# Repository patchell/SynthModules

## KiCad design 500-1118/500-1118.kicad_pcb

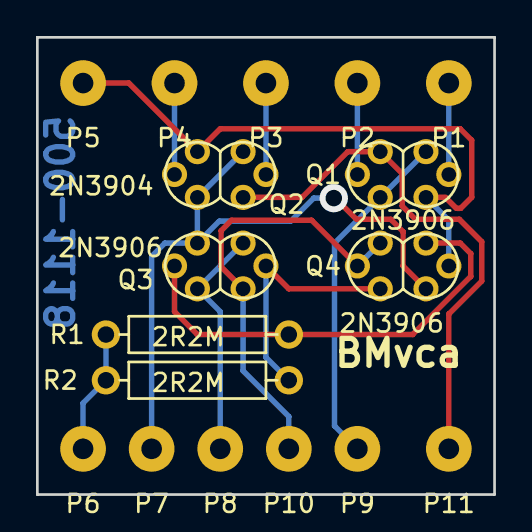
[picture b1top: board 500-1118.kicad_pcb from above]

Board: 2 copper layers, 25.4 x 25.4 mm, 17 parts (0 on the bottom side), 12 nets.

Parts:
P1: Vc+P; PAD
P2: Vc-P; PAD
P3: Vc+N; PAD
P4: Vc-N; PAD
P5: Ii; PAD
P6: Vcc; PAD
P7: Ieen; PAD
P8: Ibias; PAD
P9: Ieep; PAD
P10: Bal; PAD
P11: Io; PAD
Q1, Q3, Q4: 2N3906; DUAL_TO92
Q2: 2N3904; DUAL_TO92
R1, R2: 2R2M; AXIAL0.4

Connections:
unnamed: P1.1, Q1.2
unnamed: P3.1, Q2.5
unnamed: P4.1, Q2.2
unnamed: P5.1, Q1.3, Q2.3, Q4.2
unnamed: P6.1, R1.1, R2.1
unnamed: P7.1, Q2.1, Q2.4, Q3.3, Q4.3
unnamed: P8.1, Q3.1, Q3.4
unnamed: P9.1, Q1.1, Q1.4
unnamed: P10.1, Q3.6, Q4.5, Q4.6
unnamed: P11.1, Q1.6, Q2.6
unnamed: Q3.2, Q4.1, R1.2
unnamed: Q3.5, Q4.4, R2.2

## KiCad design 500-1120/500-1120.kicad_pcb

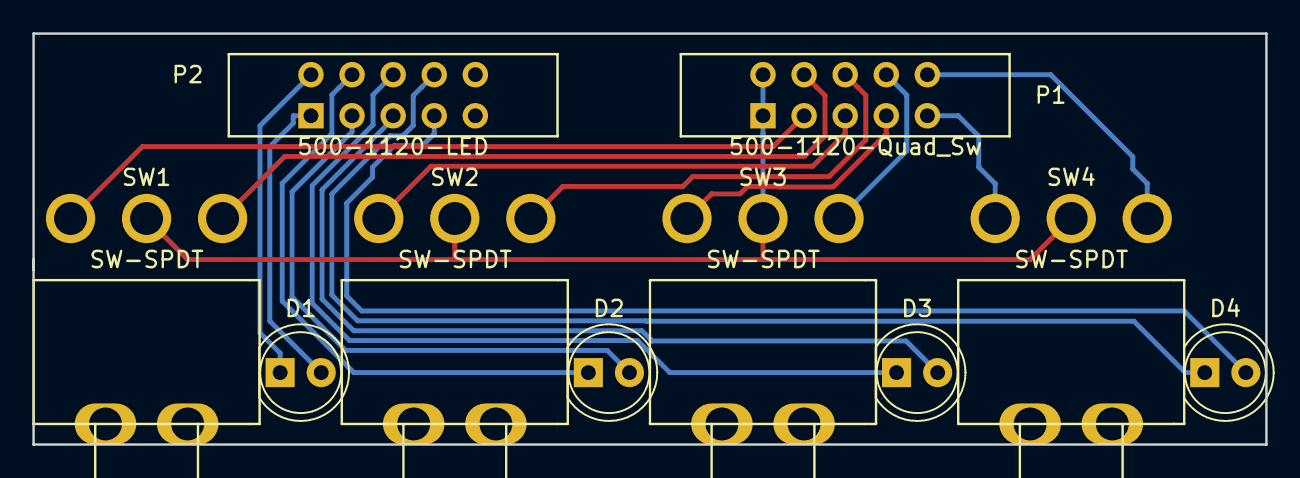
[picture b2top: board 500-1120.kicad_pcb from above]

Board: 2 copper layers, 76.2 x 25.4 mm, 10 parts (0 on the bottom side), 17 nets.

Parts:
D1, D2, D3, D4: LED; LED_5.0mm
P1: 500-1120-Quad_Sw; IDC5x2_Vert
P2: 500-1120-LED; IDC5x2_Vert
SW1, SW2, SW3, SW4: SW-SPDT; E-Switch-M6-SPDT

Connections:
unnamed: D1.1, P2.2
unnamed: D1.2, P2.1
unnamed: D2.1, P2.4
unnamed: D2.2, P2.3
unnamed: D3.1, P2.6
unnamed: D3.2, P2.5
unnamed: D4.1, P2.8
unnamed: D4.2, P2.7
unnamed: P1.1, P1.2, SW1.2, SW2.2, SW3.2, SW4.2
unnamed: P1.3, SW1.3
unnamed: P1.4, SW1.1
unnamed: P1.5, SW2.3
unnamed: P1.6, SW2.1
unnamed: P1.7, SW3.3
unnamed: P1.8, SW3.1
unnamed: P1.9, SW4.3
unnamed: P1.10, SW4.1

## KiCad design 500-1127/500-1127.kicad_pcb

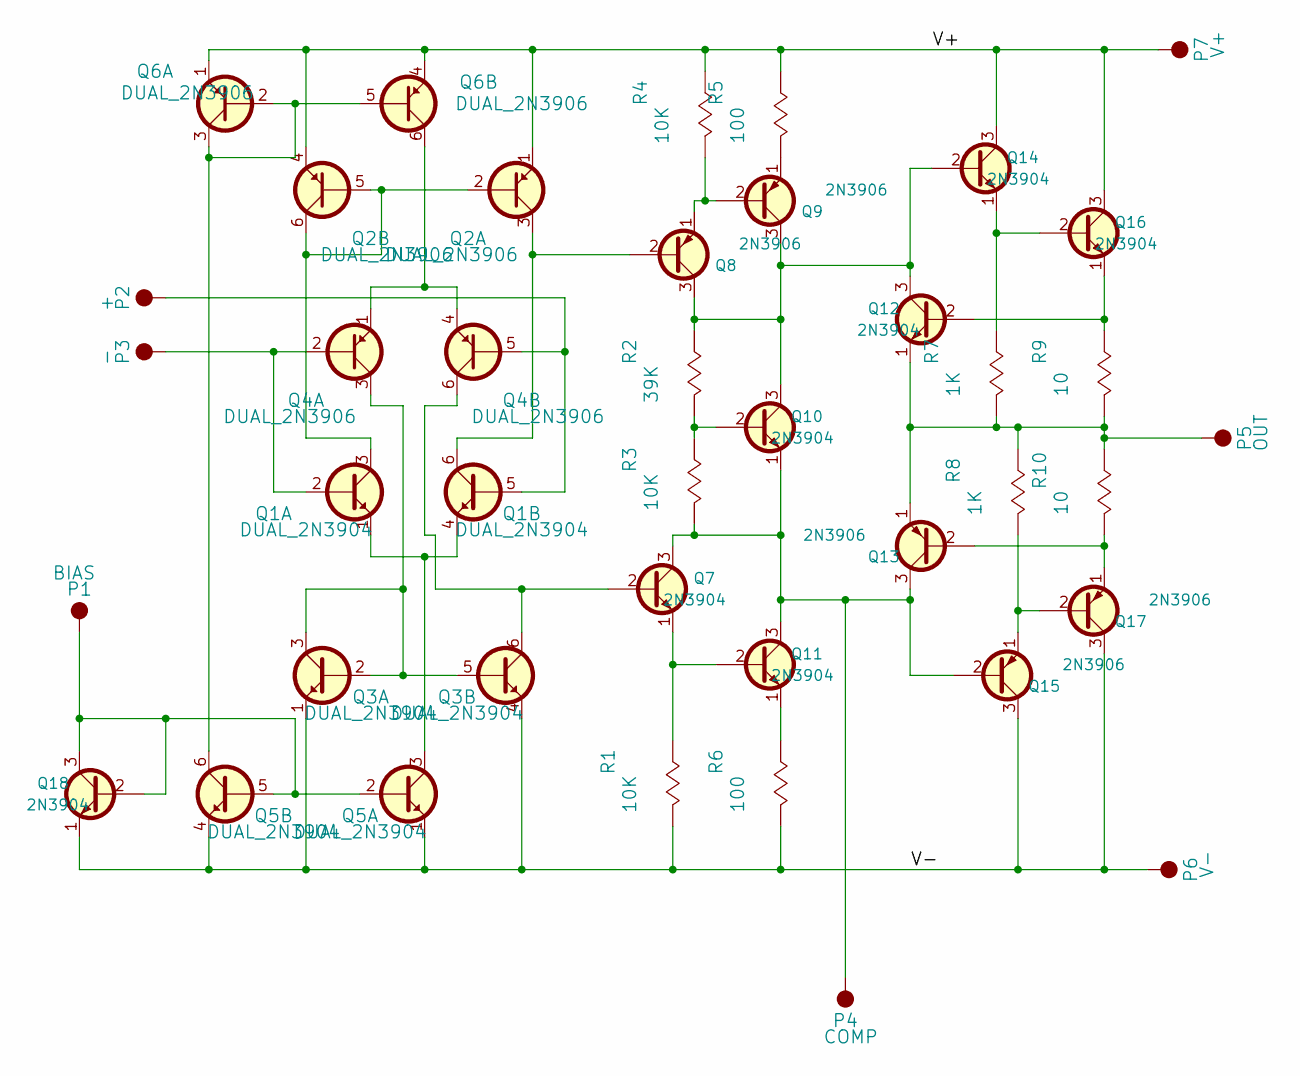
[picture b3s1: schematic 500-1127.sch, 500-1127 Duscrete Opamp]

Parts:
P1: BIAS; PAD
P2: +; PAD
P3: -; PAD
P4: COMP; PAD
P5: OUT; PAD
P6: V-; PAD
P7: V+; PAD
Q1, Q3, Q5: DUAL_2N3904; DUAL_TO92
Q2, Q4, Q6: DUAL_2N3906; DUAL_TO92
Q7, Q10, Q11, Q12, Q14, Q16, Q18: 2N3904; TO92
Q8, Q9, Q13, Q15, Q17: 2N3906; TO92
R1, R3, R4: 10K; RAD_R
R2: 39K; RAD_R
R5, R6: 100; RAD_R
R7, R8: 1K; RAD_R
R9, R10: 10; RAD_R

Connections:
unnamed: P1.1, Q5.2 (Base), Q5.5 (Base), Q18.2 (B), Q18.3 (C)
unnamed: P2.1, Q1.5 (Base), Q4.5 (Base)
unnamed: P3.1, Q1.2 (Base), Q4.2 (Base)
unnamed: P4.1, Q7.3 (C), Q10.1 (E), Q11.3 (C), Q13.3 (C), Q15.2 (B), R3.2 (B)
unnamed: P5.1, Q12.1 (E), Q13.1 (E), R7.2 (B), R8.1 (A), R9.2 (B), R10.1 (A)
unnamed: P6.1, Q3.1 (EMITTER), Q3.4 (EMITTER), Q5.1 (EMITTER), Q5.4 (EMITTER), Q15.3 (C), Q17.3 (C), Q18.1 (E), R1.2 (B), R6.2 (B)
unnamed: P7.1, Q2.1 (Emitter), Q2.4 (Emitter), Q6.1 (Emitter), Q6.4 (Emitter), Q14.3 (C), Q16.3 (C), R4.1 (A), R5.1 (A)
unnamed: Q1.1 (EMITTER), Q1.4 (EMITTER), Q5.3 (Collector)
unnamed: Q1.3 (Collector), Q2.2 (Base), Q2.5 (Base), Q2.6 (Collector)
unnamed: Q1.6 (Collector), Q2.3 (Collector), Q8.2 (B)
unnamed: Q3.2 (Base), Q3.3 (Collector), Q3.5 (Base), Q4.3 (Collector)
unnamed: Q3.6 (Collector), Q4.6 (Collector), Q7.2 (B)
unnamed: Q4.1 (Emitter), Q4.4 (Emitter), Q6.6 (Collector)
unnamed: Q5.6 (Collector), Q6.2 (Base), Q6.3 (Collector), Q6.5 (Base)
unnamed: Q8.1 (E), Q9.2 (B), R4.2 (B)
unnamed: Q9.1 (E), R5.2 (B)
unnamed: Q10.2 (B), R2.2 (B), R3.1 (A)
unnamed: Q8.3 (C), Q9.3 (C), Q10.3 (C), Q12.3 (C), Q14.2 (B), R2.1 (A)
unnamed: Q11.1 (E), R6.1 (A)
unnamed: Q7.1 (E), Q11.2 (B), R1.1 (A)
unnamed: Q12.2 (B), Q16.1 (E), R9.1 (A)
unnamed: Q13.2 (B), Q17.1 (E), R10.2 (B)
unnamed: Q14.1 (E), Q16.2 (B), R7.1 (A)
unnamed: Q15.1 (E), Q17.2 (B), R8.2 (B)

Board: 2 copper layers, 35 parts (0 on the bottom side), 24 nets, no tracks yet.

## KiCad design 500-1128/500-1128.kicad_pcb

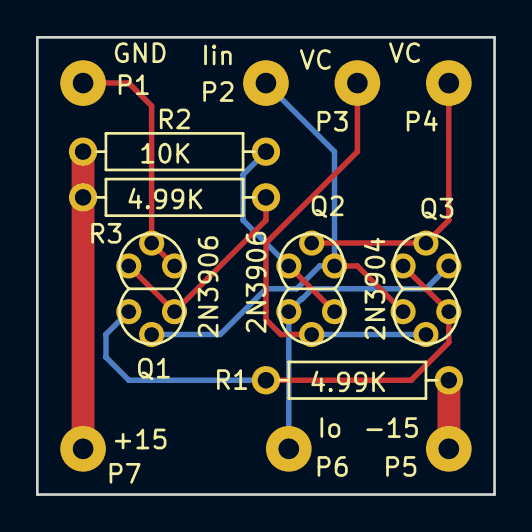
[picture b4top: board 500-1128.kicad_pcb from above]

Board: 2 copper layers, 25.4 x 25.4 mm, 13 parts (0 on the bottom side), 10 nets.

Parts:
P1: GND; PAD
P2: Iin; PAD
P3, P4: VC; PAD
P5: -15; PAD
P6: Io; PAD
P7: +15; PAD
Q1, Q2: 2N3906; DUAL_TO92
Q3: 2N3904; DUAL_TO92
R1, R3: 4.99K; AXIAL0.4
R2: 10K; AXIAL0.4

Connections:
/V+: P7.1, R2.1, R3.1
/V-: P5.1, R1.2
unnamed: P1.1, Q1.5, Q1.6
unnamed: P2.1, Q1.2, Q2.3, Q3.3
unnamed: P3.1, Q2.5, Q3.2
unnamed: P4.1, Q2.2, Q3.5
unnamed: P6.1, Q2.6, Q3.6
unnamed: Q1.1, Q1.4, R3.2
unnamed: Q1.3, Q3.1, Q3.4, R1.1
unnamed: Q2.1, Q2.4, R2.2

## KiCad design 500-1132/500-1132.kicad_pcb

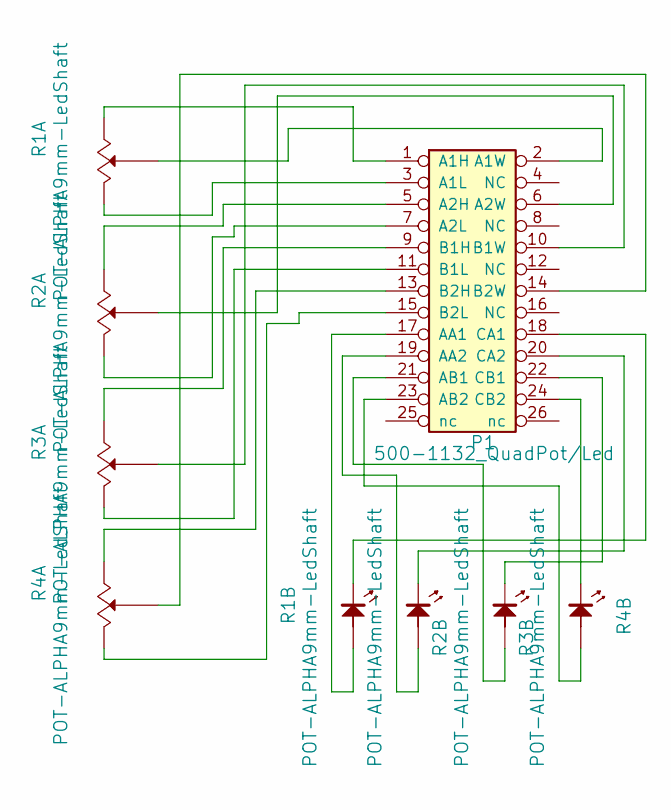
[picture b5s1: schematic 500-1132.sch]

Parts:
P1: 500-1132_QuadPot/Led; IDC-13x2
R1, R2, R3, R4: POT-ALPHA9mm-LedShaft; Alpha9mmPotWithLED

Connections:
unnamed: P1.1 (A1H), R1.1 (A)
unnamed: P1.2 (A1W), R1.2 (Wiper)
unnamed: P1.3 (A1L), R1.3 (B)
unnamed: P1.5 (A2H), R2.1 (A)
unnamed: P1.6 (A2W), R2.2 (Wiper)
unnamed: P1.7 (A2L), R2.3 (B)
unnamed: P1.9 (B1H), R3.1 (A)
unnamed: P1.10 (B1W), R3.2 (Wiper)
unnamed: P1.11 (B1L), R3.3 (B)
unnamed: P1.13 (B2H), R4.1 (A)
unnamed: P1.14 (B2W), R4.2 (Wiper)
unnamed: P1.15 (B2L), R4.3 (B)
unnamed: P1.17 (AA1), R1.5 (ANODE)
unnamed: P1.18 (CA1), R1.4 (CATHODE)
unnamed: P1.19 (AA2), R2.5 (ANODE)
unnamed: P1.20 (CA2), R2.4 (CATHODE)
unnamed: P1.21 (AB1), R3.5 (ANODE)
unnamed: P1.22 (CB1), R3.4 (CATHODE)
unnamed: P1.23 (AB2), R4.5 (ANODE)
unnamed: P1.24 (CB2), R4.4 (CATHODE)

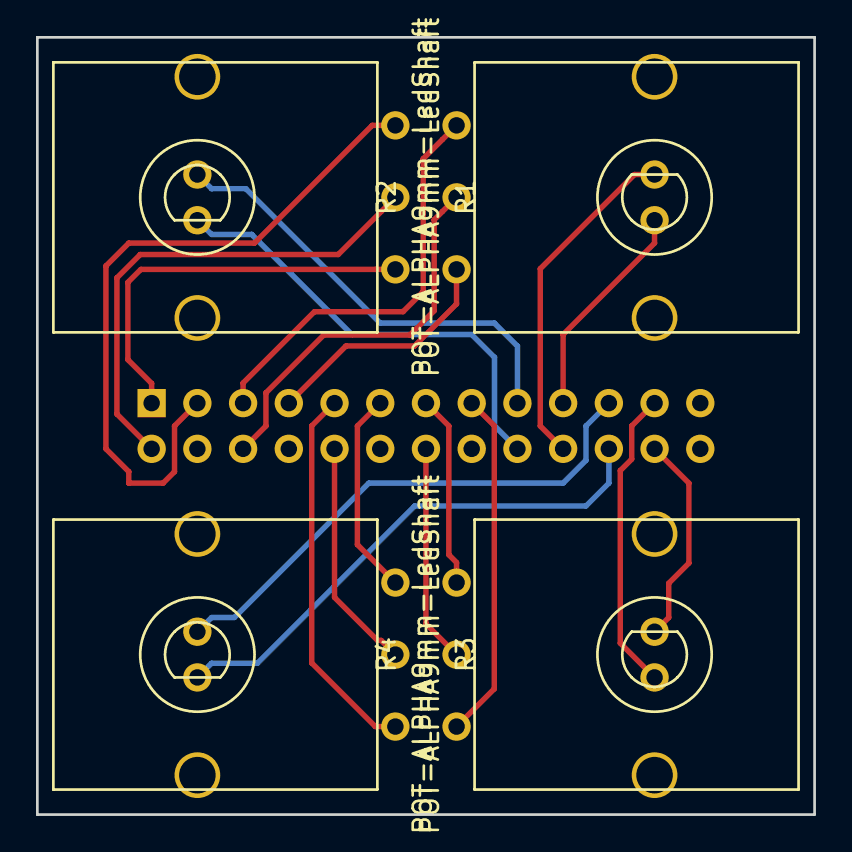
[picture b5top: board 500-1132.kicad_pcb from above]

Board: 2 copper layers, 43.2 x 43.2 mm, 5 parts (1 on the bottom side), 20 nets.

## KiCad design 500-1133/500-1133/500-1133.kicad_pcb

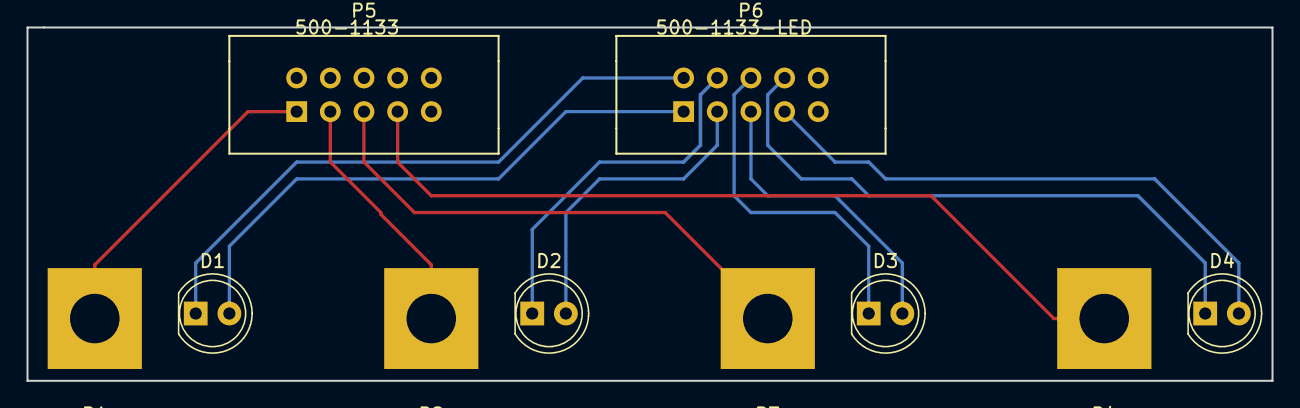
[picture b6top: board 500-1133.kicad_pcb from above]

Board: 2 copper layers, 94.0 x 26.7 mm, 10 parts (0 on the bottom side), 12 nets.

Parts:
D1, D2, D3, D4: LED_ALT; LED_5.0mm
P1, P2, P3, P4: PAD-KF2-256; KF2-256-TerminalPad
P5: 500-1133; IDC5x2_Vert
P6: 500-1133-LED; IDC5x2_Vert

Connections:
unnamed: D1.1, P6.2
unnamed: D1.2, P6.1
unnamed: D2.1, P6.4
unnamed: D2.2, P6.3
unnamed: D3.1, P6.6
unnamed: D3.2, P6.5
unnamed: D4.1, P6.8
unnamed: D4.2, P6.7
unnamed: P1.1, P5.1
unnamed: P2.1, P5.3
unnamed: P3.1, P5.5
unnamed: P4.1, P5.7
